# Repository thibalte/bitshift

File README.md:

# Bitshift

Thibault Brevet, _Bitshift_, 2015

16 printed circuit boards (10x10cm PCB, white soldermask), blue thermochromatic pigment, power supply.

Bitshift explores the physical manifestation of a digital signal bit shifting along autonomous modules. Each module integrates electronic on the back-side able to register an input signal. When triggered, each module switches on an integrated heating pattern traced on its front-side. When reaching 37°c, the blue thermochromatic pigment turns transparent, revealing the white undercoating. After executing the heating sequence, a pulse is sent to the next module. The pigment eventually fades back to blue as it cools down.

On view during [Re-programmed Art: An Open Manifesto](http://www.reprogrammed-art.cc/) at Swiss Institute in Milan, IT.

### Technical details

PCBs have been sent to the fab house specifying a white soldermask, 35um copper thickness, all rest is standard. PCBs heating panel is designed to act as a 4 Ohm resistor, with a 12V power supply it sinks 3A and dissipates about 36W and warms 20°C above a target 21°C ambient temperature. The thermochromatic pigment used has a threshold temperature of 37°C, in line with the heating panel max temperature of 41°C.

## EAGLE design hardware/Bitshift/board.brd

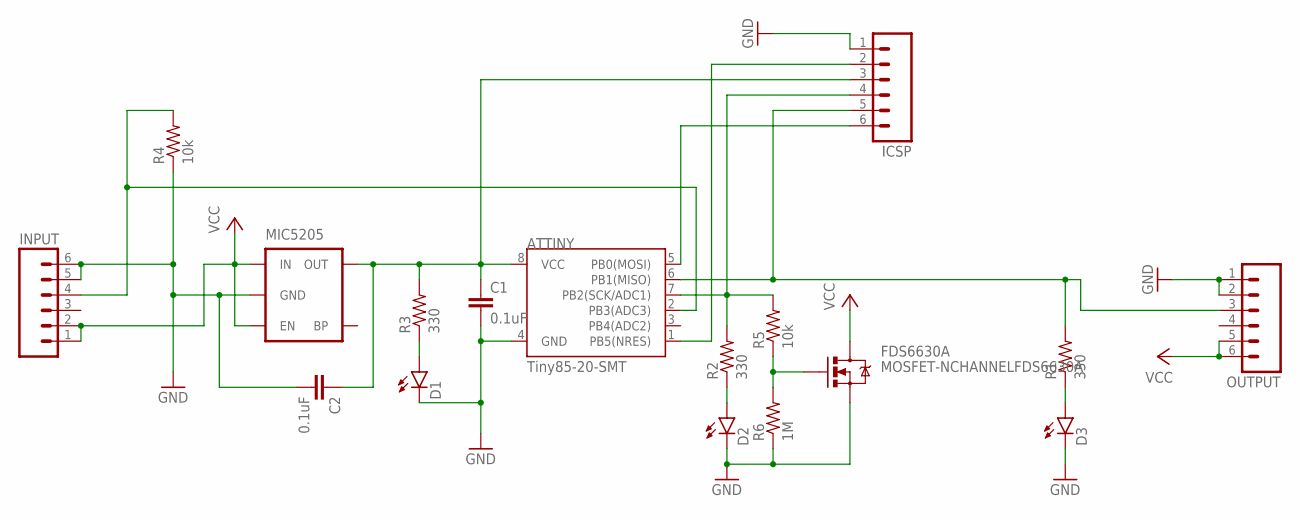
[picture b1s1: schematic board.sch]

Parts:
ATTINY: Tiny85-20-SMT; SO08-EIAJ
C1, C2: 0.1uF; 0805
D1, D2, D3: LED0603; LED-0603
FDS6630A: MOSFET-NCHANNELFDS6630A; SO08
ICSP: M06SMD-FEMALE-V2; 1X06-SMD-FEMALE-V2
INPUT: M06SMD-FEMALE-V2; 1X06-SMD-FEMALE-V2
MIC5205: MIC52055V; SOT23-5
OUTPUT: M06SMD-FEMALE-V2; 1X06-SMD-FEMALE-V2
R1, R2, R3: 330; 0603-RES
R4: 10k; 0603-RES
R5: 10k; 0805
R6: 1M; 0805

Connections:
GND: ATTINY.4 (GND), C1.2, C2.2, D1.C, D2.C, D3.C, FDS6630A.1 (S), FDS6630A.2 (S), FDS6630A.3 (S), ICSP.1, INPUT.5, INPUT.6, MIC5205.2 (GND), OUTPUT.1, OUTPUT.2, R4.1, R6.1
unnamed: D1.A, R3.1
unnamed: D2.A, R2.1
unnamed: D3.A, R1.1
unnamed: ATTINY.8 (VCC), C1.1, C2.1, ICSP.3, MIC5205.5 (OUT), R3.2
unnamed: ATTINY.2 (PB3(ADC3)), INPUT.4, R4.2
unnamed: ATTINY.6 (PB1(MISO)), ICSP.5, OUTPUT.3, R1.2
unnamed: ATTINY.5 (PB0(MOSI)), ICSP.6
unnamed: FDS6630A.4 (G), R5.1, R6.2
unnamed: ATTINY.7 (PB2(SCK/ADC1)), ICSP.4, R2.2, R5.2
unnamed: ATTINY.1 (PB5(NRES)), ICSP.2
VCC: FDS6630A.5 (D), FDS6630A.6 (D), FDS6630A.7 (D), FDS6630A.8 (D), INPUT.1, INPUT.2, MIC5205.1 (IN), MIC5205.3 (EN), OUTPUT.5, OUTPUT.6

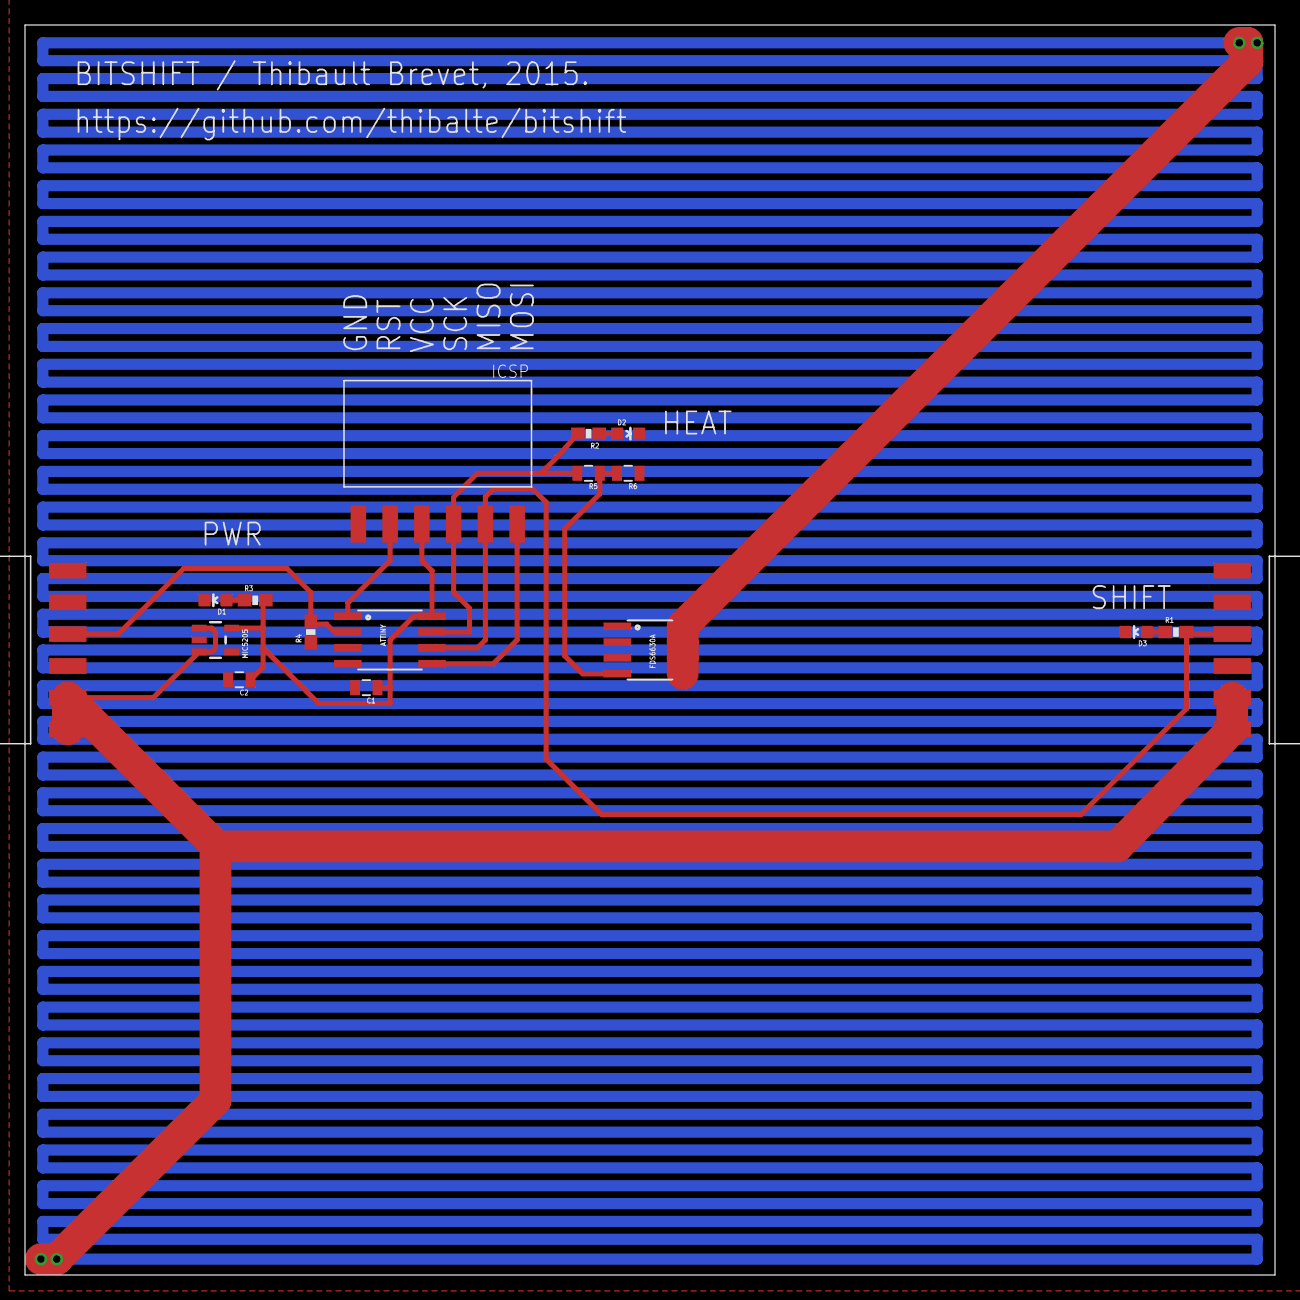
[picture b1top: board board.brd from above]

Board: 2 copper layers, 100.0 x 100.0 mm, 17 parts (0 on the bottom side), 12 nets.

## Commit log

2015-02-20 added abstract
2015-02-20 added eagle files
2015-02-20 added firmware, added pull-down resistor for IN signal
2015-02-20 added .gitignore
2015-02-22 added BOM, added ICSP header to board
2015-02-22 edited readme
2015-02-22 changed BOM into MD table
2015-02-22 removed url in BOM
2015-02-22 added connectors to BOM
2015-02-22 added decoupling cap for voltage regulator in BOM
2015-02-22 moved things around
2015-02-22 exported gerber files
2015-02-23 cleanup board files
2015-02-23 edited readme with technical details
2015-02-23 removed DS_Store
2015-03-01 removed .epf
2015-03-01 gitignore for eagle projects
2015-03-05 added firmware for master board with intervallometer trigger pulse
2015-03-06 added image to readme
2015-03-20 edited image

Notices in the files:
parts and their libraries:
SparkFun-DigitalIC: Licensing: Creative Commons ShareAlike 4.0 International - https://creativecommons.org/licenses/by-sa/4.0
